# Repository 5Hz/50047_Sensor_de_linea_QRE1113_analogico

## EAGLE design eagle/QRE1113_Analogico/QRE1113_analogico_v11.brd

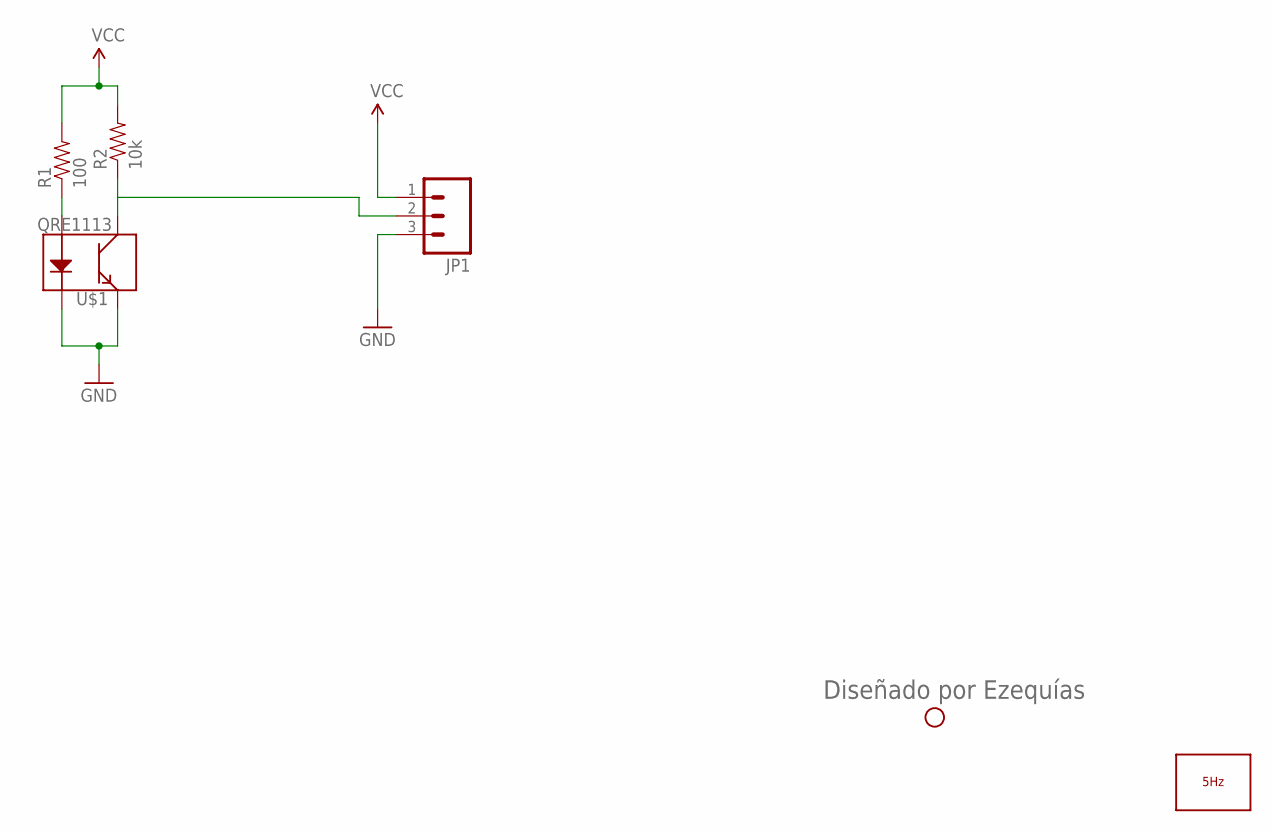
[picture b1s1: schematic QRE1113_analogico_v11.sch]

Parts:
JP1: M03PTH; 1X03
JP2: STAND-OFF
LOGO1: LOGO_5HZ_CIRC_5MM; 5HZ_LOGO_CIRC_5MM
R1: 100; 0603-RES
R2: 10k; 0603-RES
U$1: QRE1113

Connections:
10K: JP1.2, R2.1, U$1.3 (C)
GND: JP1.3, U$1.2 (K), U$1.4 (E)
unnamed: R1.1, U$1.1 (A)
VCC: JP1.1, R1.2, R2.2

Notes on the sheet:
Diseñado por Ezequías

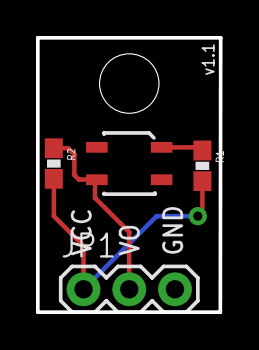
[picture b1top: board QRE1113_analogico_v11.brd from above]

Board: 2 copper layers, 10.2 x 15.2 mm, 6 parts (1 on the bottom side), 4 nets.

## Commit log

2014-01-13 creación
